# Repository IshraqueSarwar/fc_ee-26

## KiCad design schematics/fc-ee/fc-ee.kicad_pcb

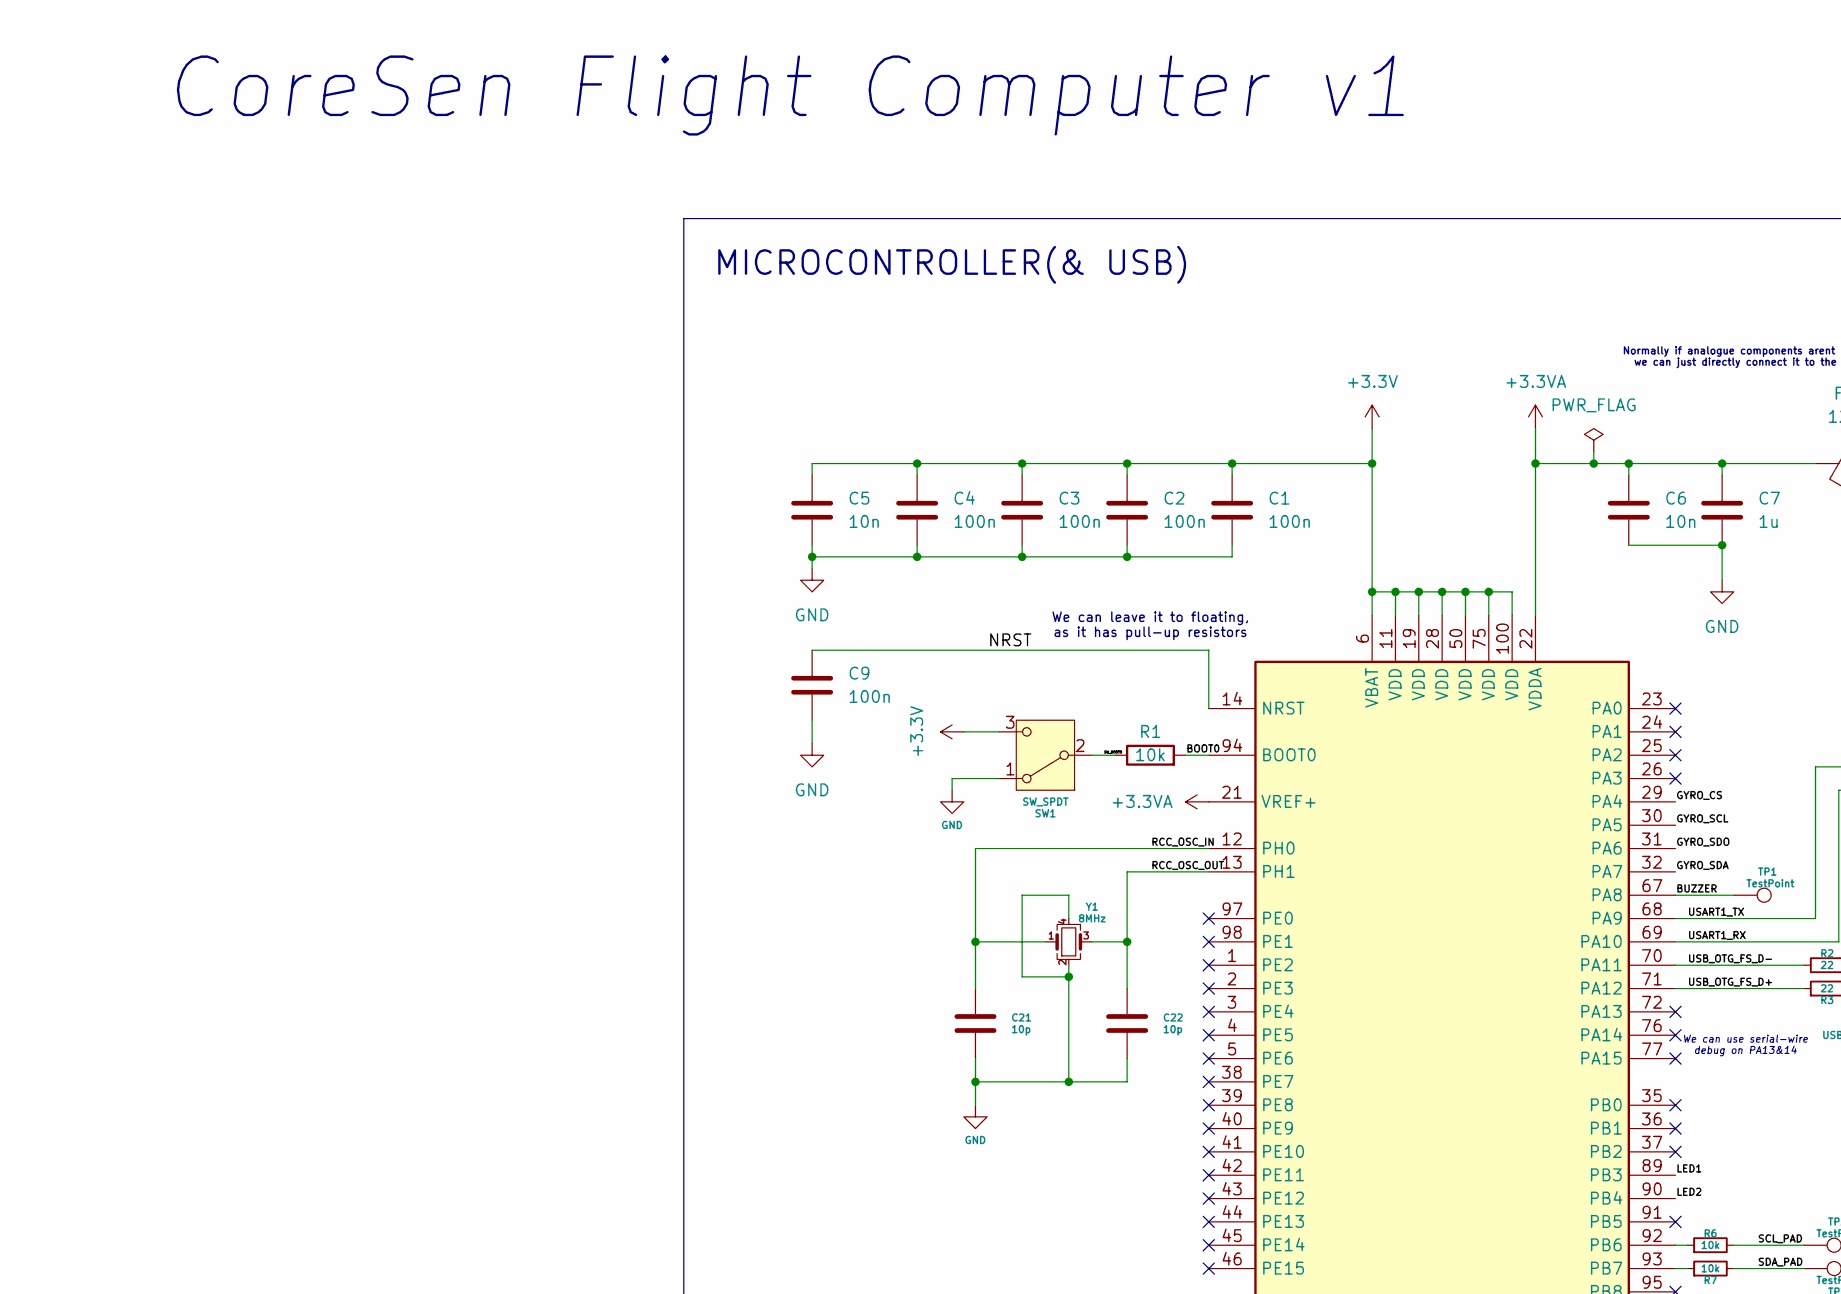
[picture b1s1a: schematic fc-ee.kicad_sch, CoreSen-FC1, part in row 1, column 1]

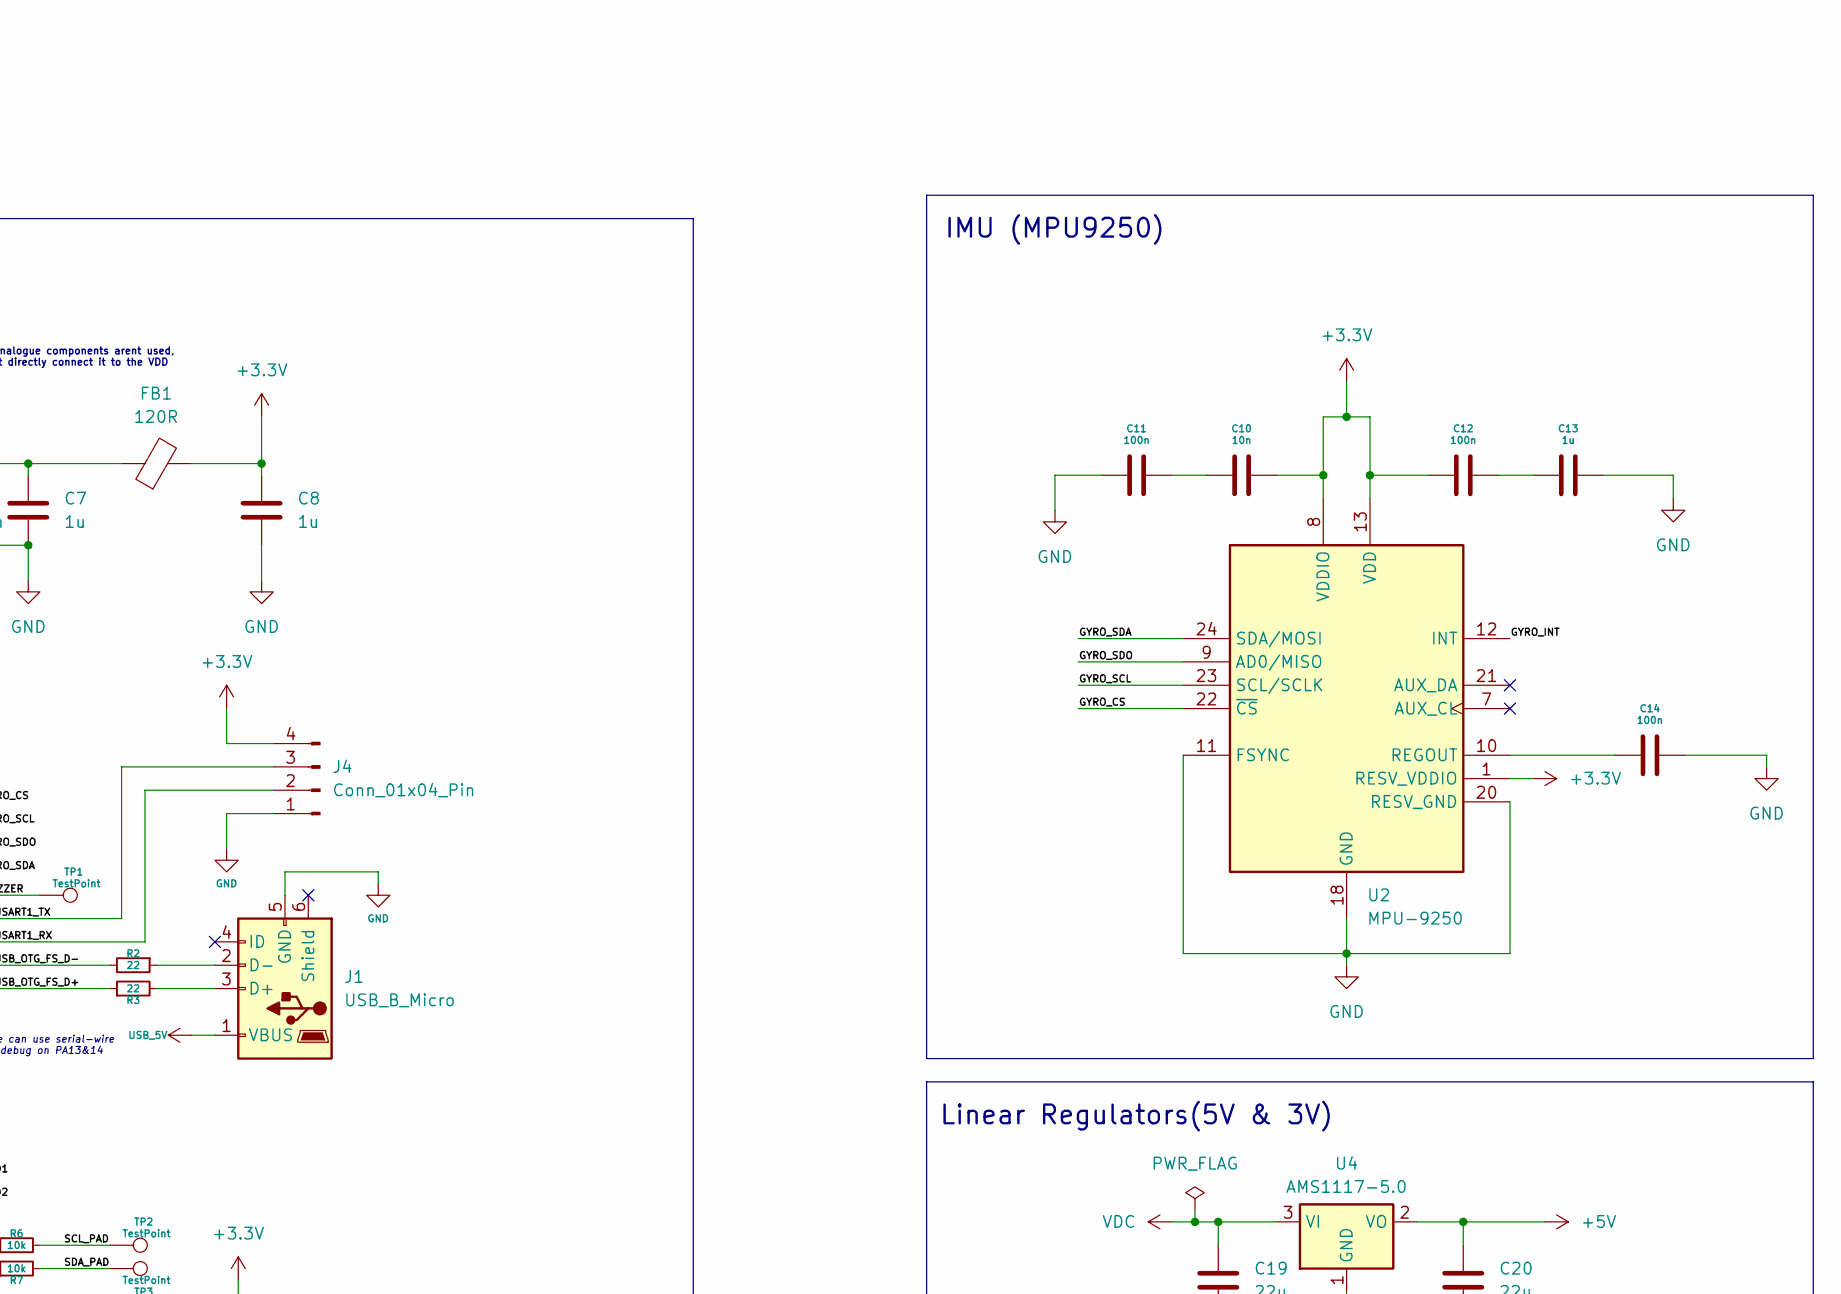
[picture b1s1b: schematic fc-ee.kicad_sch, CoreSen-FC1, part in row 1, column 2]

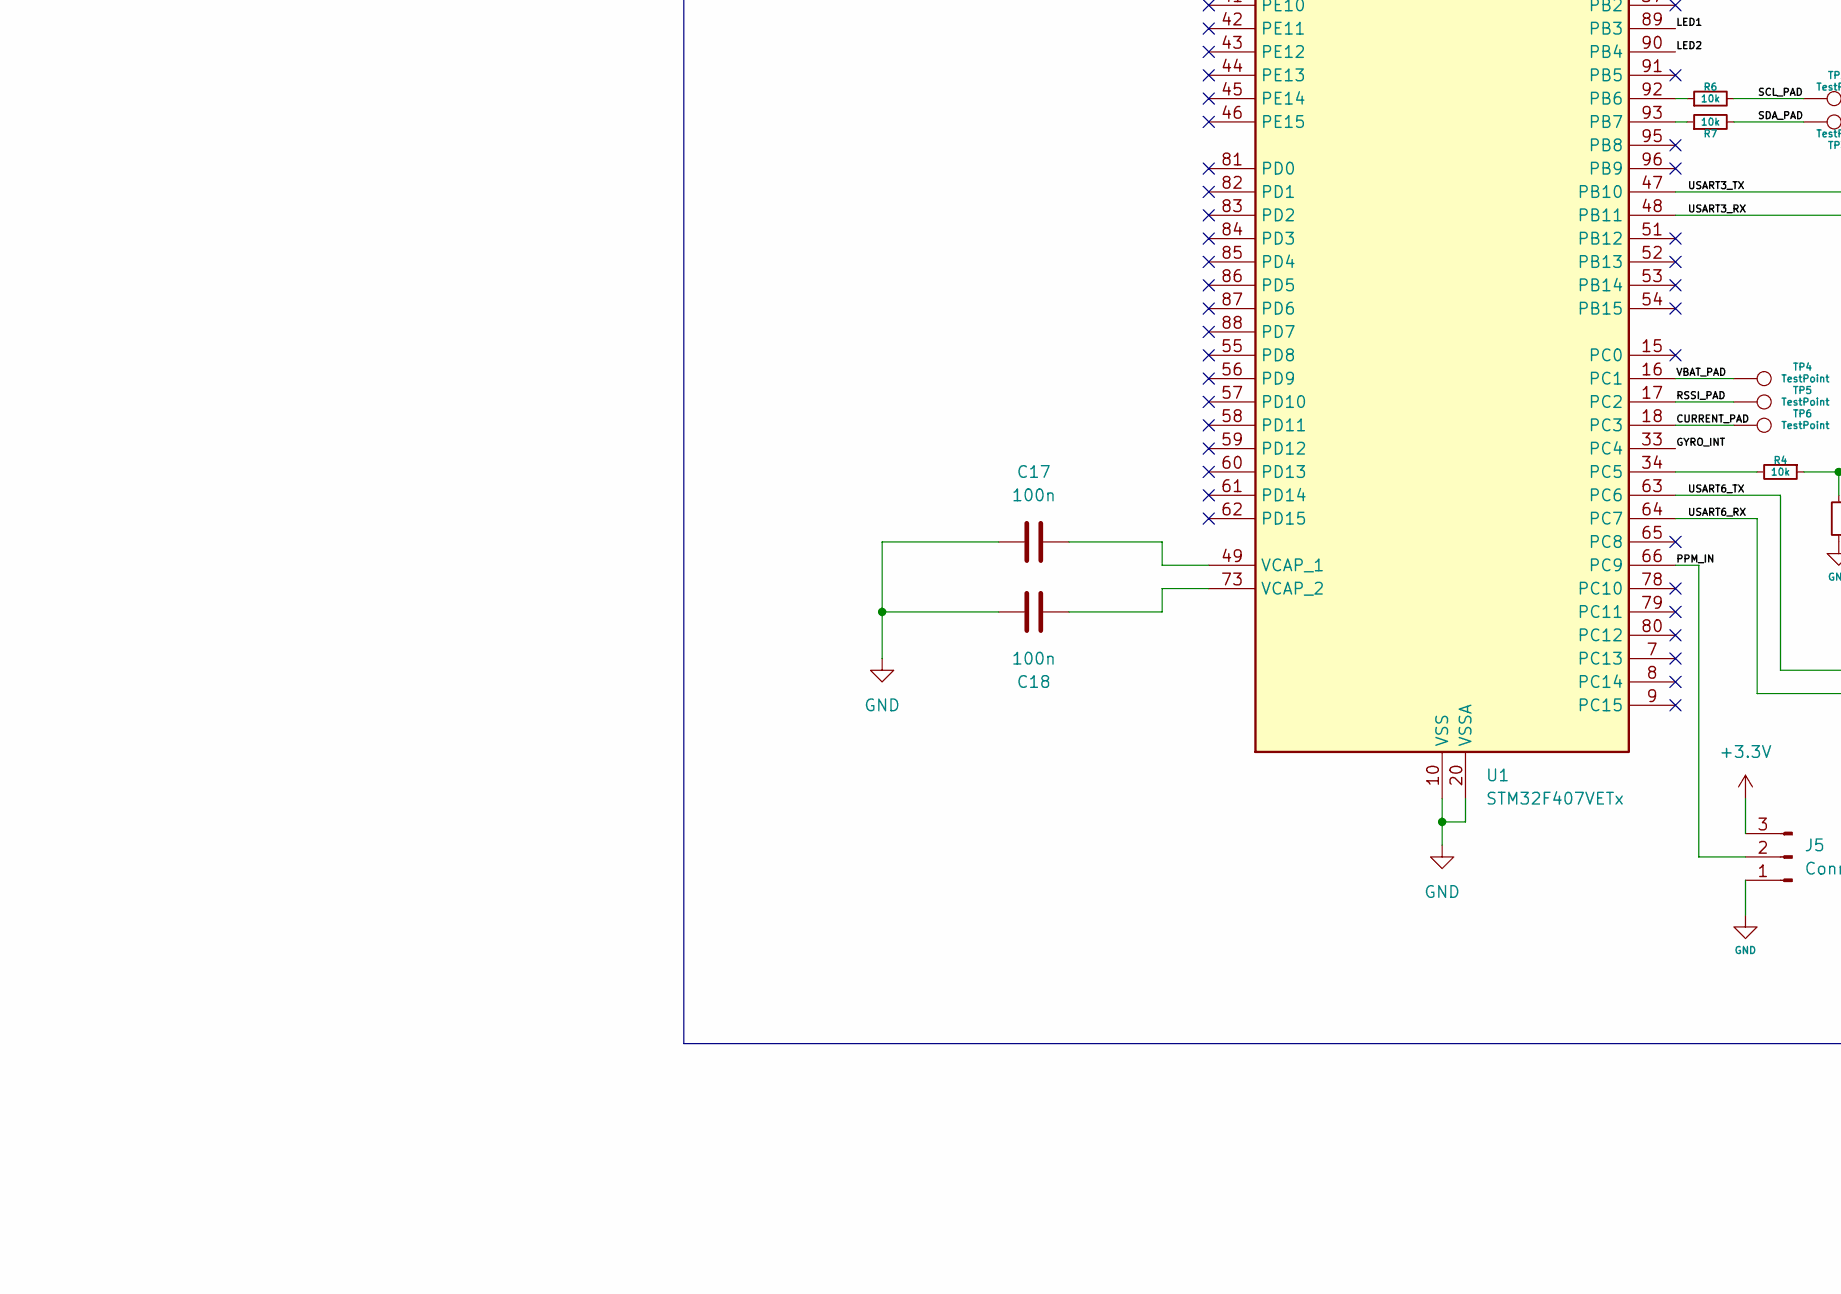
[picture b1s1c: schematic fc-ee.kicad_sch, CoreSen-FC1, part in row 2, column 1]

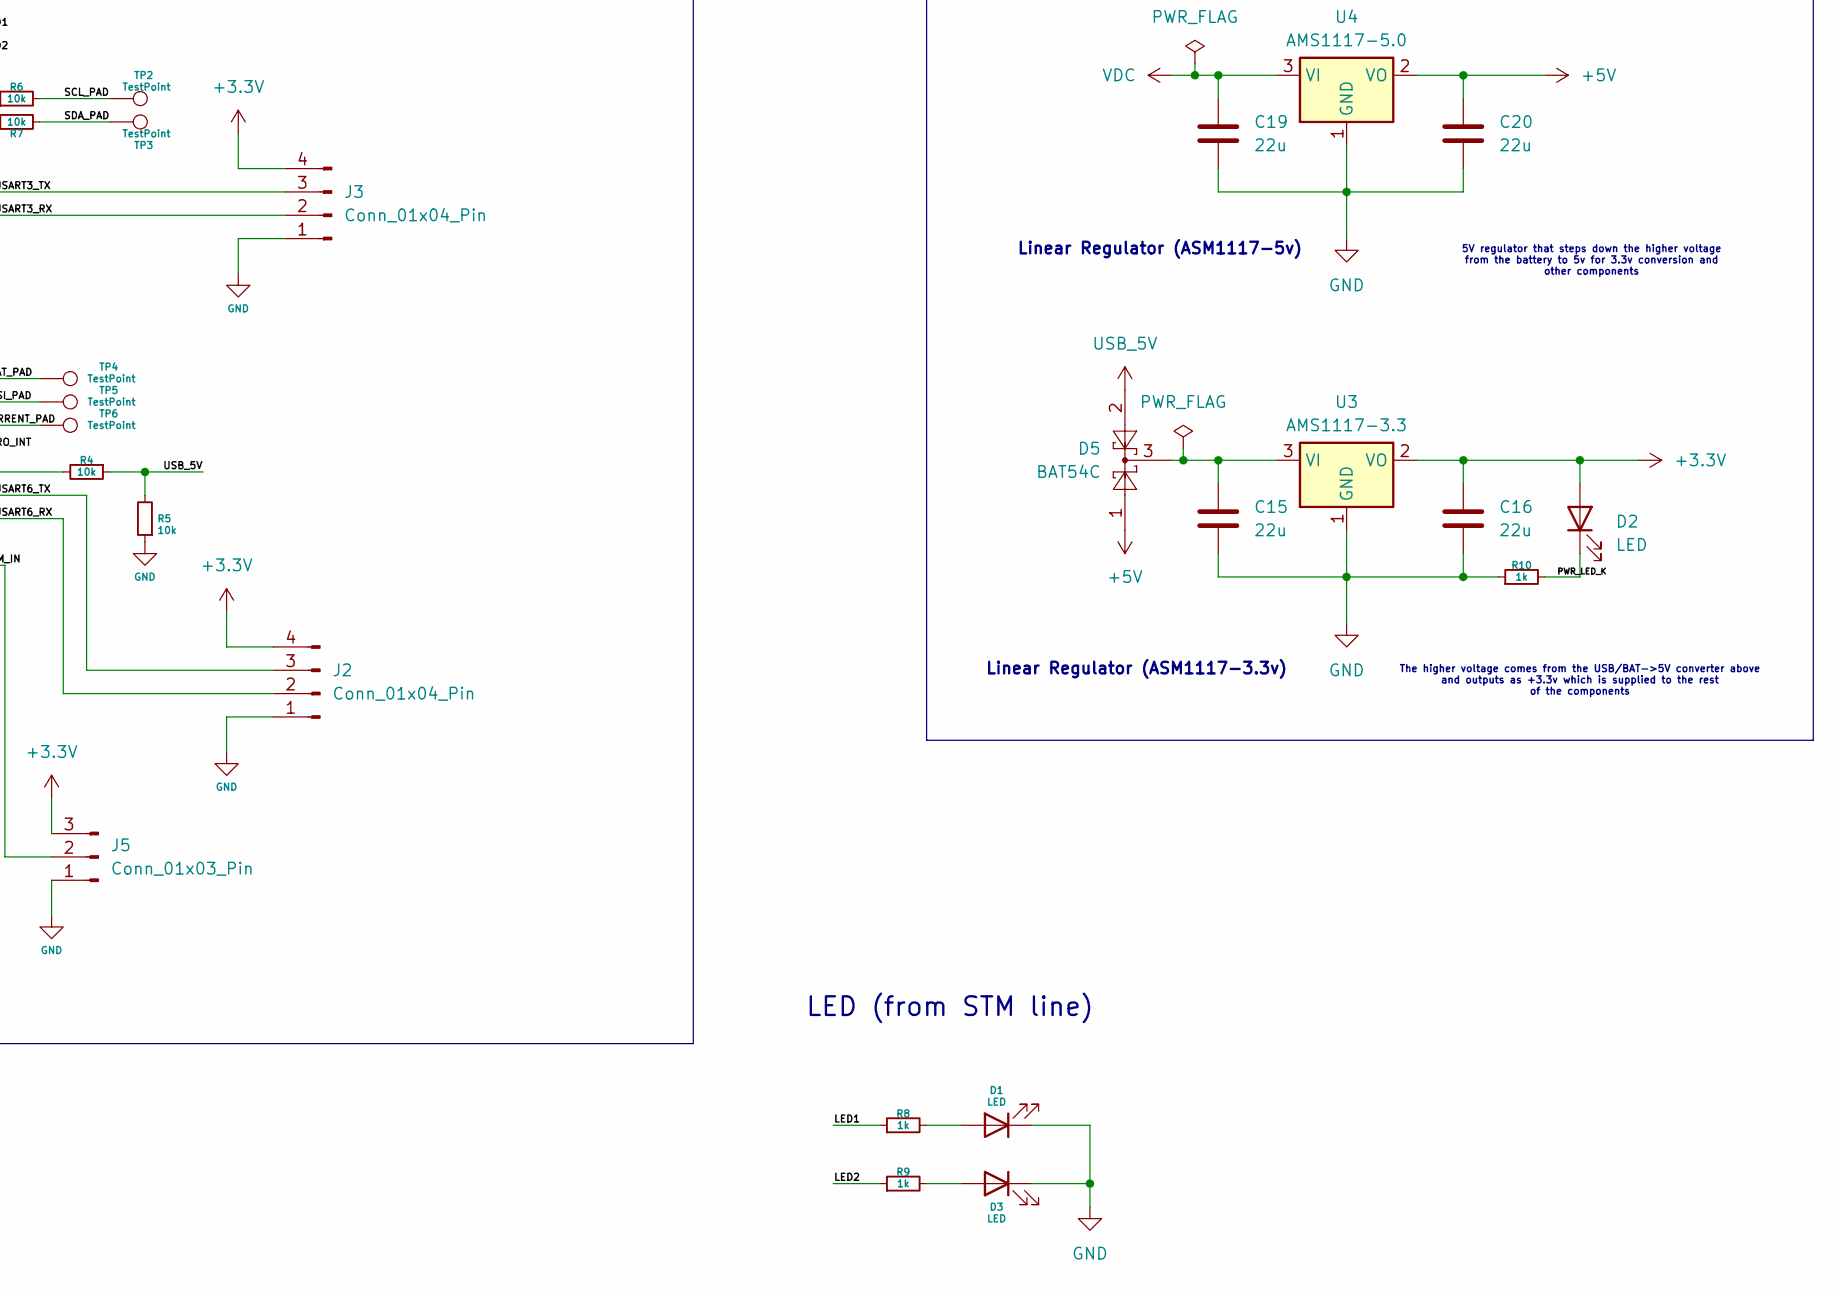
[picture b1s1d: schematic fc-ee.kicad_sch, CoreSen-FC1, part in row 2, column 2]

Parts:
C1, C2, C3, C4, C9, C11, C12, C14, C17, C18: 100n; C_0402_1005Metric
C5, C6, C10: 10n; C_0603_1608Metric
C7, C8, C13: 1u; C_0402_1005Metric
C15, C16, C19, C20: 22u; C_0805_2012Metric
C21, C22: 10p; C_0603_1608Metric
D1, D2, D3: LED; LED_0201_0603Metric
D5: BAT54C; SOT-23
FB1: 120R; L_0603_1608Metric
J1: USB_B_Micro; USB_Micro-B_Molex_47346-0001
J2, J3, J4: Conn_01x04_Pin; PinHeader_1x04_P2.00mm_Vertical
J5: Conn_01x03_Pin; JST_NV_B03P-NV_1x03_P5.00mm_Vertical
R1, R4, R5, R6, R7: 10k; R_0402_1005Metric
R2, R3: 22; R_0402_1005Metric
R8, R9, R10: 1k; R_0402_1005Metric
SW1: SW_SPDT; SW_E-Switch_EG1224_SPDT_Angled
TP1, TP2, TP3, TP4, TP5, TP6: TestPoint; TestPoint_Pad_D4.0mm
U1: STM32F407VETx; LQFP-100_14x14mm_P0.5mm
U2: MPU-9250; InvenSense_QFN-24_3x3mm_P0.4mm
U3: AMS1117-3.3; SOT-223-3_TabPin2
U4: AMS1117-5.0; SOT-223-3_TabPin2
Y1: 8MHz; Crystal_SMD_3225-4Pin_3.2x2.5mm_HandSoldering

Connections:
+3.3V: C1.1, C2.1, C3.1, C4.1, C5.1, C8.1, C10.2, C12.1, C16.1, D2.2 (A), FB1.2, J2.4, J3.4, J4.4, J5.3, SW1.3 (C), U1.6 (VBAT), U1.11 (VDD), U1.19 (VDD), U1.28 (VDD), U1.50 (VDD), U1.75 (VDD), U1.100 (VDD), U2.1 (RESV_VDDIO), U2.8 (VDDIO), U2.13 (VDD), U3.2 (VO)
+3.3VA: C6.1, C7.1, FB1.1, U1.21 (VREF+), U1.22 (VDDA)
+5V: C20.1, D5.1, U4.2 (VO)
/BOOT0: R1.2, U1.94 (BOOT0)
/BUZZER: TP1.1, U1.67 (PA8)
/CURRENT_PAD: TP6.1, U1.18 (PC3)
/GYRO_CS: U1.29 (PA4), U2.22 (~CS)
/GYRO_INT: U1.33 (PC4), U2.12 (INT)
/GYRO_SCL: U1.30 (PA5), U2.23 (SCL/SCLK)
/GYRO_SDA: U1.32 (PA7), U2.24 (SDA/MOSI)
/GYRO_SDO: U1.31 (PA6), U2.9 (AD0/MISO)
/LED1: R8.1, U1.89 (PB3)
/LED2: R9.1, U1.90 (PB4)
/NRST: C9.1, U1.14 (NRST)
/PPM_IN: J5.2, U1.66 (PC9)
/PWR_LED_K: D2.1 (K), R10.2
/RCC_OSC_IN: C21.1, U1.12 (PH0), Y1.1
/RCC_OSC_OUT: C22.1, U1.13 (PH1), Y1.3
/RSSI_PAD: TP5.1, U1.17 (PC2)
/SCL_PAD: R6.2, TP2.1
/SDA_PAD: R7.2, TP3.1
/SW_BOOT0: R1.1, SW1.2 (B)
/USART1_RX: J4.2, U1.69 (PA10)
/USART1_TX: J4.3, U1.68 (PA9)
/USART3_RX: J3.2, U1.48 (PB11)
/USART3_TX: J3.3, U1.47 (PB10)
/USART6_RX: J2.2, U1.64 (PC7)
/USART6_TX: J2.3, U1.63 (PC6)
/USB_OTG_FS_D+: R3.1, U1.71 (PA12)
/USB_OTG_FS_D-: R2.2, U1.70 (PA11)
/VBAT_PAD: TP4.1, U1.16 (PC1)
GND: C1.2, C2.2, C3.2, C4.2, C5.2, C6.2, C7.2, C8.2, C9.2, C11.1, C13.2, C14.2, C15.2, C16.2, C17.1, C18.1, C19.2, C20.2, C21.2, C22.2, D1.1 (K), D3.1 (K), J1.5 (GND), J2.1, J3.1, J4.1, J5.1, R5.1, R10.1, SW1.1 (A), U1.10 (VSS), U1.20 (VSSA), U1.27 (VSS), U1.74 (VSS), U1.99 (VSS), U2.11 (FSYNC), U2.18 (GND), U2.20 (RESV_GND), U3.1 (GND), U4.1 (GND), Y1.2, Y1.4
unnamed: C10.1, C11.2
unnamed: C12.2, C13.1
unnamed: D1.2 (A), R8.2
unnamed: D3.2 (A), R9.2
unnamed: J1.3 (D+), R3.2
unnamed: J1.2 (D-), R2.1
unnamed: R6.1, U1.92 (PB6)
unnamed: R7.1, U1.93 (PB7)
unnamed: R4.2, U1.34 (PC5)
unnamed: C17.2, U1.49 (VCAP_1)
unnamed: C18.2, U1.73 (VCAP_2)
unnamed: C14.1, U2.10 (REGOUT)
unnamed: C15.1, D5.3, U3.3 (VI)
USB_5V: D5.2, J1.1 (VBUS), R4.1, R5.2
VDC: C19.1, U4.3 (VI)

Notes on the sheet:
Linear Regulators(5V & 3V)
We can leave it to floating, as it has pull-up resistors
We can use serial-wire debug on PA13&14
IMU (MPU9250)
The higher voltage comes from the USB/BAT->5V converter above and outputs as +3.3v which is supplied to the rest of the components
Normally if analogue components arent used, we can just directly connect it to the VDD
MICROCONTROLLER(& USB)
5V regulator that steps down the higher voltage from the battery to 5v for 3.3v conversion and other components
LED (from STM line)
Linear Regulator (ASM1117-3.3v)
CoreSen Flight Computer v1
Linear Regulator (ASM1117-5v)

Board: 2 copper layers, 54 parts (0 on the bottom side), 47 nets, no tracks yet.

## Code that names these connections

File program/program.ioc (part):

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Mcu.Name=STM32F407V(E-G)Tx
Mcu.Package=LQFP100
Mcu.UserName=STM32F407VETx
PA10.Mode=Asynchronous
PA10.Signal=USART1_RX
PA11.Mode=Device_Only
PA11.Signal=USB_OTG_FS_DM
PA12.Mode=Device_Only
PA12.Signal=USB_OTG_FS_DP
PA4.GPIOParameters=GPIO_Label
PA4.GPIO_Label=GYRO_CS
PA4.Signal=GPIO_Output
PA5.GPIOParameters=GPIO_Label
PA5.GPIO_Label=GYRO_SCL
PA5.Signal=SPI1_SCK
PA6.GPIOParameters=GPIO_Label
PA6.GPIO_Label=GYRO_SDO
PA6.Signal=SPI1_MISO
PA7.GPIOParameters=GPIO_Label
PA7.GPIO_Label=GYRO_SDA
PA7.Signal=SPI1_MOSI
PA8.GPIOParameters=GPIO_Label
PA8.GPIO_Label=BUZZER
PA8.Signal=GPIO_Output
PA9.Mode=Asynchronous
PA9.Signal=USART1_TX
PB10.Mode=Asynchronous
PB10.Signal=USART3_TX
PB11.Mode=Asynchronous
PB11.Signal=USART3_RX
PB3.GPIOParameters=GPIO_Label
PB3.GPIO_Label=LED1
PB3.Signal=GPIO_Output
PB4.GPIOParameters=GPIO_Label
PB4.GPIO_Label=LED2
PB4.Signal=GPIO_Output
PB6.GPIOParameters=GPIO_Label
PB6.GPIO_Label=SCL_PAD
PB6.Signal=I2C1_SCL
PB7.GPIOParameters=GPIO_Label
PB7.GPIO_Label=SDA_PAD
PB7.Signal=I2C1_SDA
PC1.GPIOParameters=GPIO_Label
PC1.GPIO_Label=VBAT_PAD
PC1.Signal=ADCx_IN11
PC2.GPIOParameters=GPIO_Label
PC2.GPIO_Label=RSSI_PAD
PC2.Signal=ADCx_IN12
PC3.GPIOParameters=GPIO_Label
PC3.GPIO_Label=CURRENT_PAD
PC3.Signal=ADCx_IN13
PC4.GPIOParameters=GPIO_Label
PC4.GPIO_Label=GYRO_INT
PC4.Signal=GPXTI4
PC5.GPIOParameters=GPIO_Label
PC5.GPIO_Label=USB_5V
PC5.Signal=ADCx_IN15
PC6.Mode=Asynchronous
PC6.Signal=USART6_TX
PC7.Mode=Asynchronous
PC7.Signal=USART6_RX
PC9.GPIOParameters=GPIO_Label
PC9.GPIO_Label=PPM_IN
PC9.Signal=S_TIM3_CH4
PH0-OSC_IN.Mode=HSE-External-Oscillator
PH0-OSC_IN.Signal=RCC_OSC_IN
PH1-OSC_OUT.Mode=HSE-External-Oscillator
PH1-OSC_OUT.Signal=RCC_OSC_OUT
RCC.HSE_VALUE=25000000
RCC.SYSCLKFreq_VALUE=16000000
board=custom

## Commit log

2026-02-16 research-2/17/26
2026-02-17 research-2/17/26-2
2026-02-22 update 2/22/26
2026-02-25 update 2/25/26
2026-02-26 update 2/26/26
2026-03-01 3/1/26
